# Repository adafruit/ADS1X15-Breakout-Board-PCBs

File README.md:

# PCB for the Adafruit 12 and 16 bit I2C ADC's with PGA

<a href="http://www.adafruit.com/products/1083"><br/>Click here to purchase one from the Adafruit shop</a>

__Format is EagleCAD schematic and board layout__

This PCB is both for [ADS1015](https://www.adafruit.com/product/1083) and [ADS1115](https://www.adafruit.com/product/1085).

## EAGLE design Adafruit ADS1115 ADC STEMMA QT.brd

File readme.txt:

This is the PCB for the Adafruit 12 and 16 bit I2C ADC's with PGA
Format is EagleCAD schematic and board layout

For more details, check out the product page at

-----> http://adafruit.com/products/1083
-----> http://adafruit.com/products/1085

Adafruit invests time and resources providing this open source design, 
please support Adafruit and open-source hardware by purchasing 
products from Adafruit!

Designed by Adafruit Industries.  
Creative Commons Attribution, Share-Alike license, check license.txt for more information
All text above must be included in any redistribution

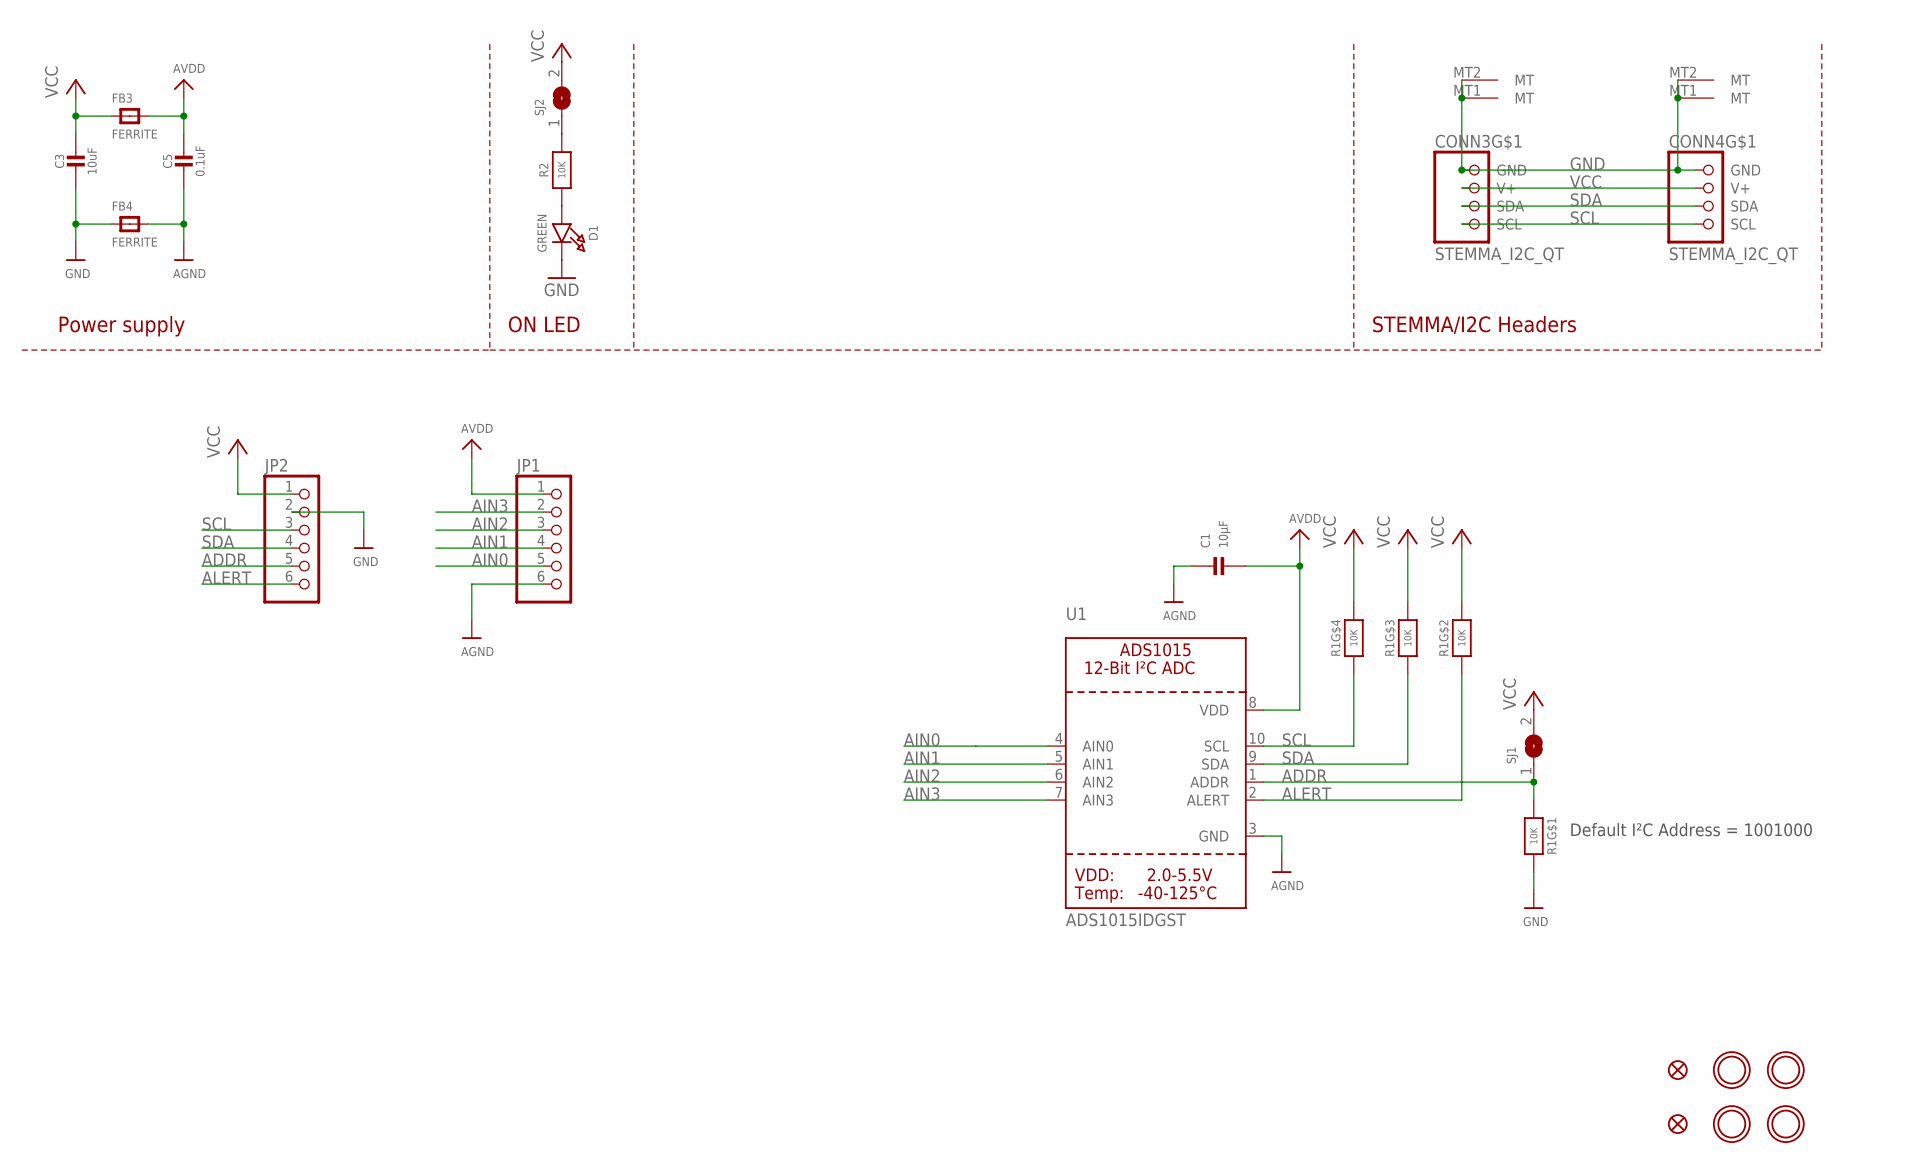
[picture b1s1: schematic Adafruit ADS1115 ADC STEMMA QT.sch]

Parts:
C1: 10µF; 0805-NO
C3: 10uF; 0805-NO
C5: 0.1uF; 0603-NO
CONN3, CONN4: STEMMA_I2C_QT; JST_SH4
D1: GREEN; CHIPLED_0603_NOOUTLINE
FB3, FB4: FERRITE; 0603-NO
FID3, FID4: FIDUCIAL_1MM
JP1, JP2: HEADER-1X670MIL; 1X06_ROUND_70
R1: 10K; RESPACK_4X0603
R2: 10K; 0603-NO
SJ1: SOLDERJUMPER; SOLDERJUMPER_ARROW_NOPASTE
SJ2: SOLDERJUMPERCLOSED; SOLDERJUMPER_CLOSEDWIRE
U1: ADS1015IDGST; MSOP10
U$25, U$27, U$29, U$30: MOUNTINGHOLE2.5; MOUNTINGHOLE_2.5_PLATED

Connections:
ADDR: JP2.5, R1.1, SJ1.1, U1.1 (ADDR)
AGND: C1.1, C5.2, FB4.2, JP1.6, U1.3 (GND)
AIN0: JP1.5, U1.4 (AIN0)
AIN1: JP1.4, U1.5 (AIN1)
AIN2: JP1.3, U1.6 (AIN2)
AIN3: JP1.2, U1.7 (AIN3)
ALERT: JP2.6, R1.2 (1), U1.2 (ALERT)
AVDD: C1.2, C5.1, FB3.2, JP1.1, U1.8 (VDD)
GND: C3.2, CONN3.1 (GND), CONN3.MT1 (MT), CONN3.MT2 (MT), CONN4.1 (GND), CONN4.MT1 (MT), CONN4.MT2 (MT), D1.C, FB4.1, JP2.2, R1.8 (2)
unnamed: R2.2, SJ2.1
unnamed: D1.A, R2.1
SCL: CONN3.4 (SCL), CONN4.4 (SCL), JP2.3, R1.4 (1), U1.10 (SCL)
SDA: CONN3.3 (SDA), CONN4.3 (SDA), JP2.4, R1.3 (1), U1.9 (SDA)
VCC: C3.1, CONN3.2 (V+), CONN4.2 (V+), FB3.1, JP2.1, R1.5 (2), R1.6 (2), R1.7 (2), SJ1.2, SJ2.2

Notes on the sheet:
STEMMA/I2C Headers
ON LED
Power supply
Default I²C Address = 1001000

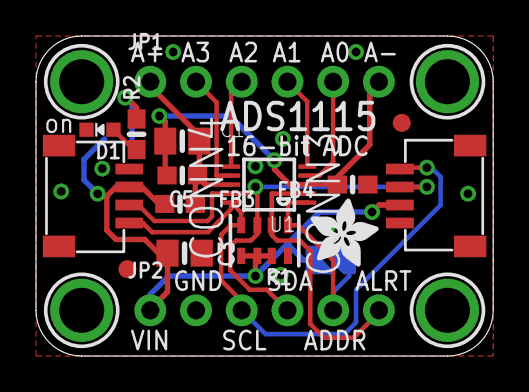
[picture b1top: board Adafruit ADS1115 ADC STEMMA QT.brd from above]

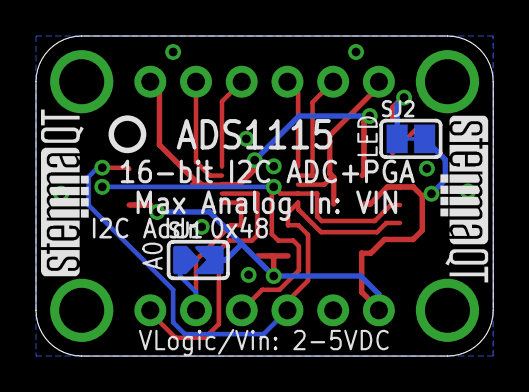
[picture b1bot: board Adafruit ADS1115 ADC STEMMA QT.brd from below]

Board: 2 copper layers, 25.4 x 17.8 mm, 25 parts (5 on the bottom side), 14 nets.

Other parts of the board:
U$32: ADAFRUIT_3.5MM
U$33: PCBFEAT-REV-040
U$34, U$35: STEMMAQT

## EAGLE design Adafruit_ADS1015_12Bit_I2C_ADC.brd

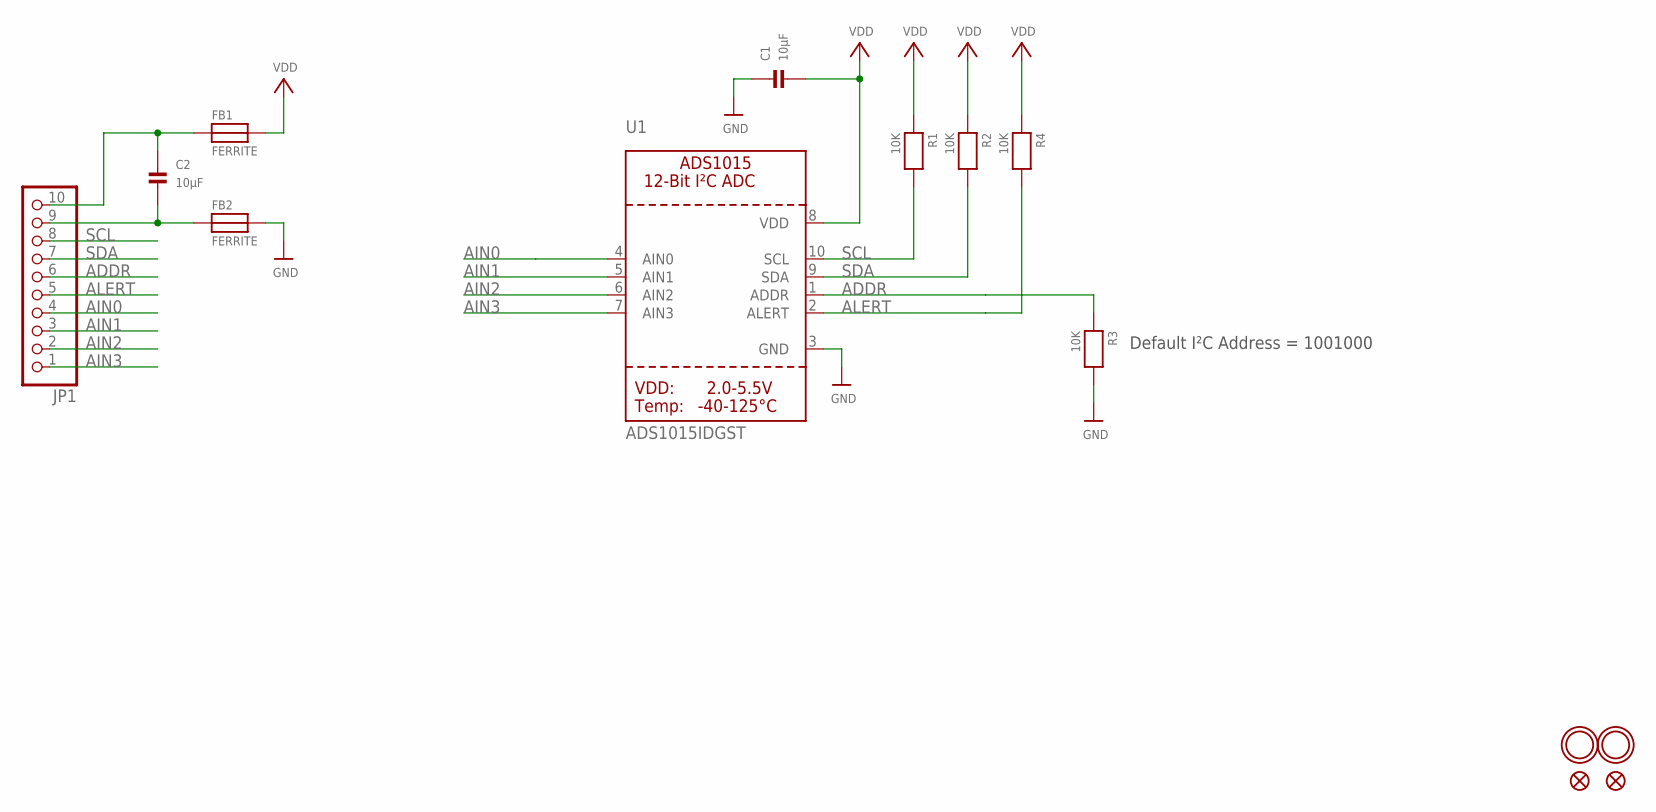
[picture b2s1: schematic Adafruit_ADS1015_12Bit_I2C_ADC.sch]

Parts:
C1, C2: 10µF; 0805
FB1, FB2: FERRITE; 0805
FID1, FID2: FIDUCIAL""; FIDUCIAL_1MM
JP1: HEADER-1X1070MIL; 1X10_ROUND70
R1, R2, R3, R4: 10K; 0805
U1: ADS1015IDGST; MSOP10
U$13, U$14: MOUNTINGHOLE2.5; MOUNTINGHOLE_2.5_PLATED

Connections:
ADDR: JP1.6, R3.1, U1.1 (ADDR)
AIN0: JP1.4, U1.4 (AIN0)
AIN1: JP1.3, U1.5 (AIN1)
AIN2: JP1.2, U1.6 (AIN2)
AIN3: JP1.1, U1.7 (AIN3)
ALERT: JP1.5, R4.2, U1.2 (ALERT)
GND: C1.1, FB2.2, R3.2, U1.3 (GND)
unnamed: C2.1, FB1.1, JP1.10
unnamed: C2.2, FB2.1, JP1.9
SCL: JP1.8, R1.2, U1.10 (SCL)
SDA: JP1.7, R2.2, U1.9 (SDA)
VDD: C1.2, FB1.2, R1.1, R2.1, R4.1, U1.8 (VDD)

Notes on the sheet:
Default I²C Address = 1001000

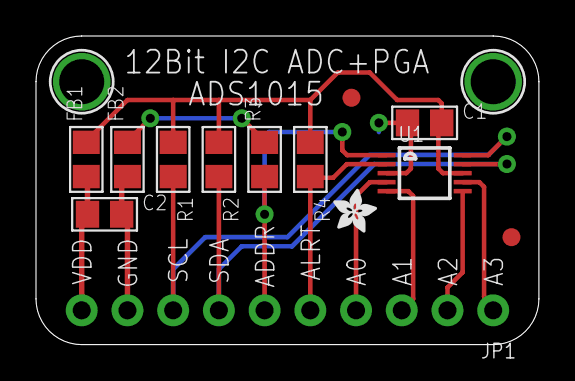
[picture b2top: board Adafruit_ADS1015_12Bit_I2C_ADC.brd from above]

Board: 2 copper layers, 27.9 x 17.1 mm, 16 parts (1 on the bottom side), 12 nets.

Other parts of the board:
U$15: ADAFRUIT_TEXT_20MM
U$16: ADAFRUIT_2.5MM

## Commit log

2012-11-23 Files!
2012-11-23 read
2012-11-23 rename
2019-04-17 new readme
2022-06-29 updating image and adding stemma eagle files
2022-06-29 updating readme
